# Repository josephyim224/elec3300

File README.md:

# Elec3300

This project builds an omni wheel car with a bluetooth remote controller. The omni wheel robot is based on STM32F103 with DRV8801 as motor driver. The controller is based on STM8S003.

## Car

### PCB Design

*Car PCB Top View*

*Car PCB Bottom View*

*see [schematic.pdf](car_hw/output/schematic.pdf)*

### 3D Print Components

*Car Motor Mount*

*Car Shaft A*

*Car Shaft B*

### Software

- Use STM32CubeIDE
- Refer to `/car_sw`

## Remote

### PCB Design

*Remote PCB Top View*

*Remote PCB Bottom View*

*see [schematic.pdf](remote_hw/output/schematic.pdf)*

### 3D Print Components

*Remote Case*

### Software

Setup:
1. `sudo apt-get install libusb-1.0-0-dev sdcc -y`
1. Get [stm8flash](https://github.com/vdudouyt/stm8flash)
1. Run `bash ./flash.sh` to compile and flash program

Reference: [Getting started with STM8 Development Tools on GNU/LINUX](https://www.codementor.io/@hbendali/)getting-started-with-stm8-development-tools-on-gnu-linux-zu59yo35x

Template: [stsw-stm8069](https://my.st.com/content/my_st_com/en/products/embedded-software/mcu-mpu-embedded-software/stm8-embedded-software/stsw-stm8069.html)

Library: [stm8s-sdcc](https://github.com/stecman/stm8s-sdcc)

## Final Deliverables

*Car Top*

*Car Bottom*

*Remote Top*

*Remote With Case*

## Progress
| urgency | difficulty | task | description | done? |
| --- | --- | --- | --- | --- |
| - | - | design pcb | | v |
| - | - | solder pcb | | v |
| - | - | mech design | | car(v), remote(v) |
| 0 | 0 | button | button | remote(v) | |
| 0 | 0 | led | led display | car(v), remote(v) |
| 1 | 1 | motor driver | (car) pwm & direction control | v |
| 1 | 2 | uart | communicate | car(v), remote(v) |
| 1 | 2 | i2c | communicate | car(v hardware), remote(v software) |
| 1 | 3 | mpu6050 (i2c) | port and simplify Adafruit version | car(v), remote(v) |
| 2 | 4 | ssd1306 lcd (i2c) | display line and text | car(v), remote(v) |
| 3 | 2 | ws2812b RGB led | display R/G/B | car(v), remote(x) |
| 4 | 1 | vibration motor | (remote) pwm output | x |
| 4 | 2 | 24c02 eeprom (i2c) | read and write data | x |
| 4 | ? | encoder | (car) encoder counter | v |
| 5 | 4 | gy530 TOF (i2c) | get distance | x |

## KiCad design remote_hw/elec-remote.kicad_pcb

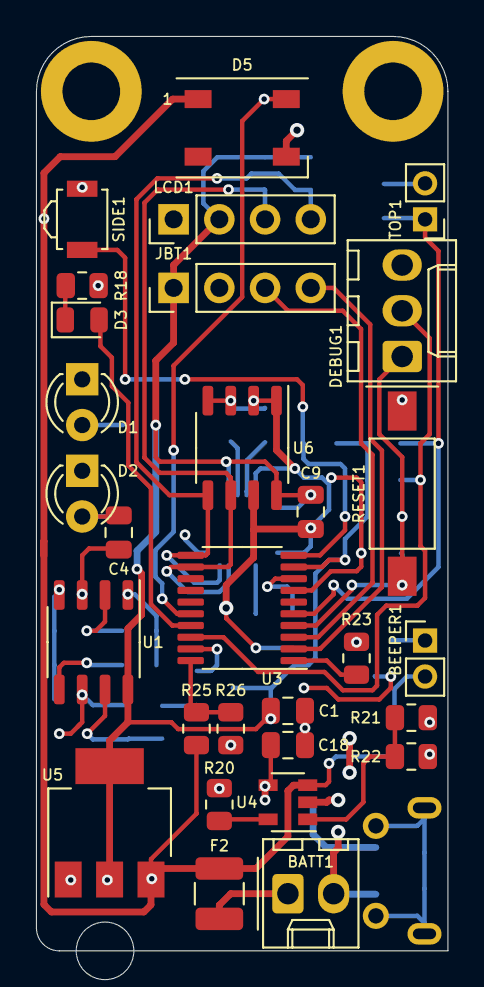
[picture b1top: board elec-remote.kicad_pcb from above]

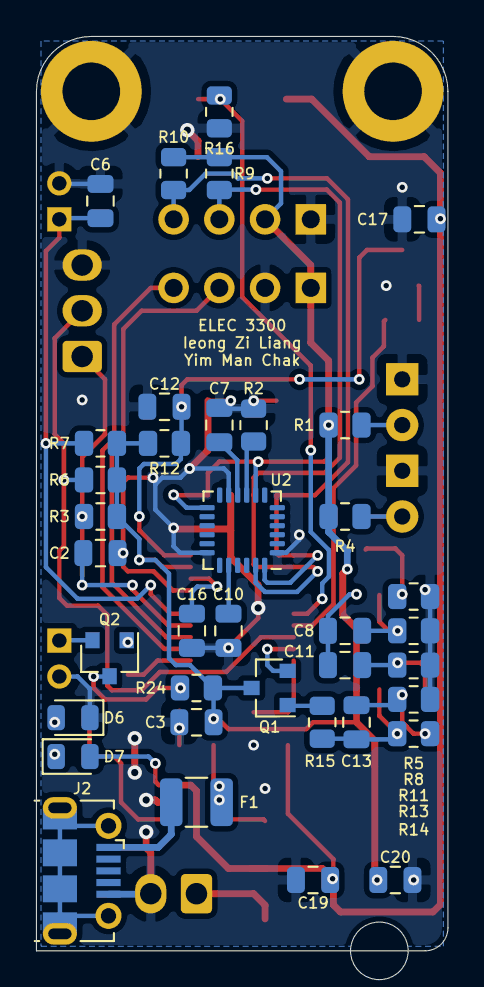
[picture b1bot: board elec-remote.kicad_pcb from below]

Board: 2 copper layers, 22.9 x 50.8 mm, 69 parts (37 on the bottom side), 40 nets.

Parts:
BATT1: BATT; Molex_KK-254_AE-6410-02A_1x02_P2.54mm_Vertical
BEEPER1: BEEPER; PinHeader_1x02_P2.00mm_Vertical
C1, C2, C4, C6, C7, C8, C9, C12, C13, C17, C20: 100n; C_0805_2012Metric
C3, C11, C16, C18, C19: 1u; C_0805_2012Metric
C10: 2200p; C_0805_2012Metric
D1: IR_Sender; LED_D3.0mm
D2: IR_Receiver; LED_D3.0mm
D3, D6, D7: LED; LED_0805_2012Metric
D5: WS2812B; LED_WS2812B_PLCC4_5.0x5.0mm_P3.2mm
DEBUG1: Conn_01x03; Molex_KK-254_AE-6410-03A_1x03_P2.54mm_Vertical
F1, F2: Fuse; Fuse_1210_3225Metric
H1, H3: MountingHole_Pad; MountingHole_3.2mm_M3_DIN965_Pad
H2: MountingHole_Pad; MountingHole_3.2mm_M3
J2: USB_B_Micro; USB_Micro-B_Molex-105017-0001
JBT1: BT; PinHeader_1x04_P2.54mm_Vertical
LCD1: LCD; PinHeader_1x04_P2.54mm_Vertical
Q1, Q2: BC817; SOT-23
R1: 220; R_0805_2012Metric
R2: 0; R_0805_2012Metric
R3, R6, R7, R9, R10, R12, R18, R21, R22, R25, R26: 4k7; R_0805_2012Metric
R4: 39k; R_0805_2012Metric
R5, R11: 68k; R_0805_2012Metric
R8: 8k2; R_0805_2012Metric
R13, R16, R23, R24: 1k; R_0805_2012Metric
R14: 470k; R_0805_2012Metric
R15: 1k8; R_0805_2012Metric
R20: 2k; R_0805_2012Metric
RESET1: SW_Push; SW_SPST_FSMSM
SIDE1: SW_Push; SW_SPST_B3U-3000P
TOP1: TOP; PinHeader_1x02_P2.00mm_Vertical
U1: LM358; SOP-8_3.9x4.9mm_P1.27mm
U2: MPU-6050; InvenSense_QFN-24_4x4mm_P0.5mm
U3: STM8S003F3P; TSSOP-20_4.4x6.5mm_P0.65mm
U4: MCP73831-2-OT; SOT-23-5
U5: AP1117-33; SOT-223-3_TabPin2
U6: 24LC00; SOP-8_3.9x4.9mm_P1.27mm

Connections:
+3V3: C1.2, C3.2, C9.2, C20.1, JBT1.1, LCD1.2, Q1.3, R1.2, R3.2, R4.2, R6.2, R7.2, R9.2, R10.2, R12.2, R24.2, U1.8, U2.8, U2.13, U3.9, U5.2, U6.8
+5V: C18.2, F1.1, U4.4
+BATT: C17.2, C19.1, D5.1, D7.2, F2.2, R25.2, U4.3, U5.3
/BATT: R25.1, R26.2, U3.20
/BEEP: R23.2, U3.1
/IR: Q1.2, U3.19
/LED0: D3.2, U3.17
/NRST: C2.2, DEBUG1.1, R3.1, RESET1.1, U3.4
/RX: JBT1.3, U3.3
/SCL: LCD1.3, R9.1, U2.23, U3.12, U6.6
/SDA: LCD1.4, R10.1, U2.24, U3.11, U6.5
/SIDE: C12.2, R12.1, SIDE1.1, U3.10
/SWIM: DEBUG1.2, R6.1, U3.18
/TOP: C6.2, R7.1, TOP1.1, U3.5
/TX: JBT1.4, U3.2
/WS2812: D5.4, R16.2, U3.16
GND: BATT1.2, BEEPER1.2, C1.1, C2.1, C3.1, C6.1, C7.1, C9.1, C10.1, C12.1, C16.1, C17.1, C18.1, C19.2, C20.2, D1.1, D2.1, D5.3, D6.1, DEBUG1.3, H1.1, H3.1, J2.5, JBT1.2, LCD1.1, R2.2, R5.1, R8.1, R11.1, R13.2, R16.1, R18.1, R20.2, R26.1, RESET1.2, SIDE1.2, TOP1.2, U1.4, U2.1, U2.11, U2.18, U3.7, U4.2, U5.1, U6.1, U6.2, U6.3, U6.4, U6.7
unnamed: BATT1.1, F2.1
unnamed: BEEPER1.1, Q2.2
unnamed: C4.1, R5.2, U1.3
unnamed: C4.2, D2.2, R4.1
unnamed: C7.2, U2.10
unnamed: C8.2, R8.2, U1.2
unnamed: C10.2, U2.20
unnamed: C11.1, R11.2, U1.5
unnamed: C8.1, C11.2, U1.1
unnamed: C13.1, R14.1, R15.2, U1.7
unnamed: C13.2, R13.1, R14.2, U1.6
unnamed: C16.2, U3.8
unnamed: D1.2, R1.1
unnamed: D3.1, R18.2
unnamed: D6.2, R21.1
unnamed: D7.1, R22.1
unnamed: F1.2, J2.1
unnamed: Q1.1, R15.1
unnamed: Q2.1, R23.1
unnamed: Q2.3, R24.1
unnamed: R2.1, U2.9
unnamed: R20.1, U4.5
unnamed: R21.2, R22.2, U4.1

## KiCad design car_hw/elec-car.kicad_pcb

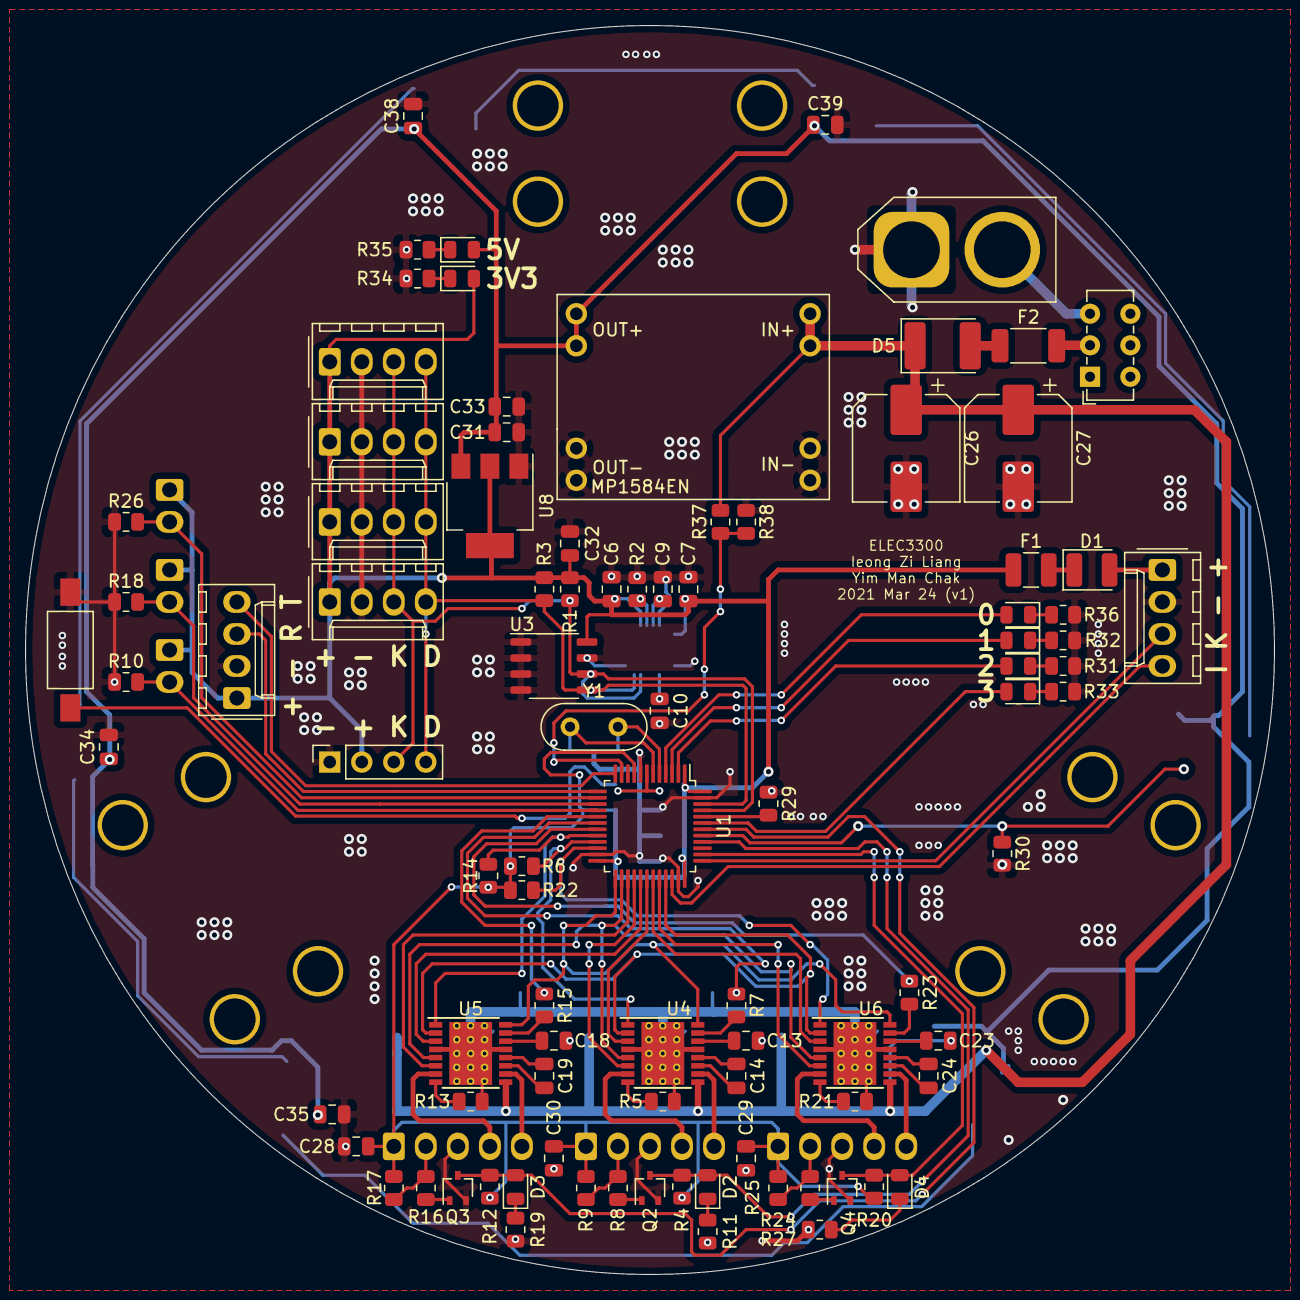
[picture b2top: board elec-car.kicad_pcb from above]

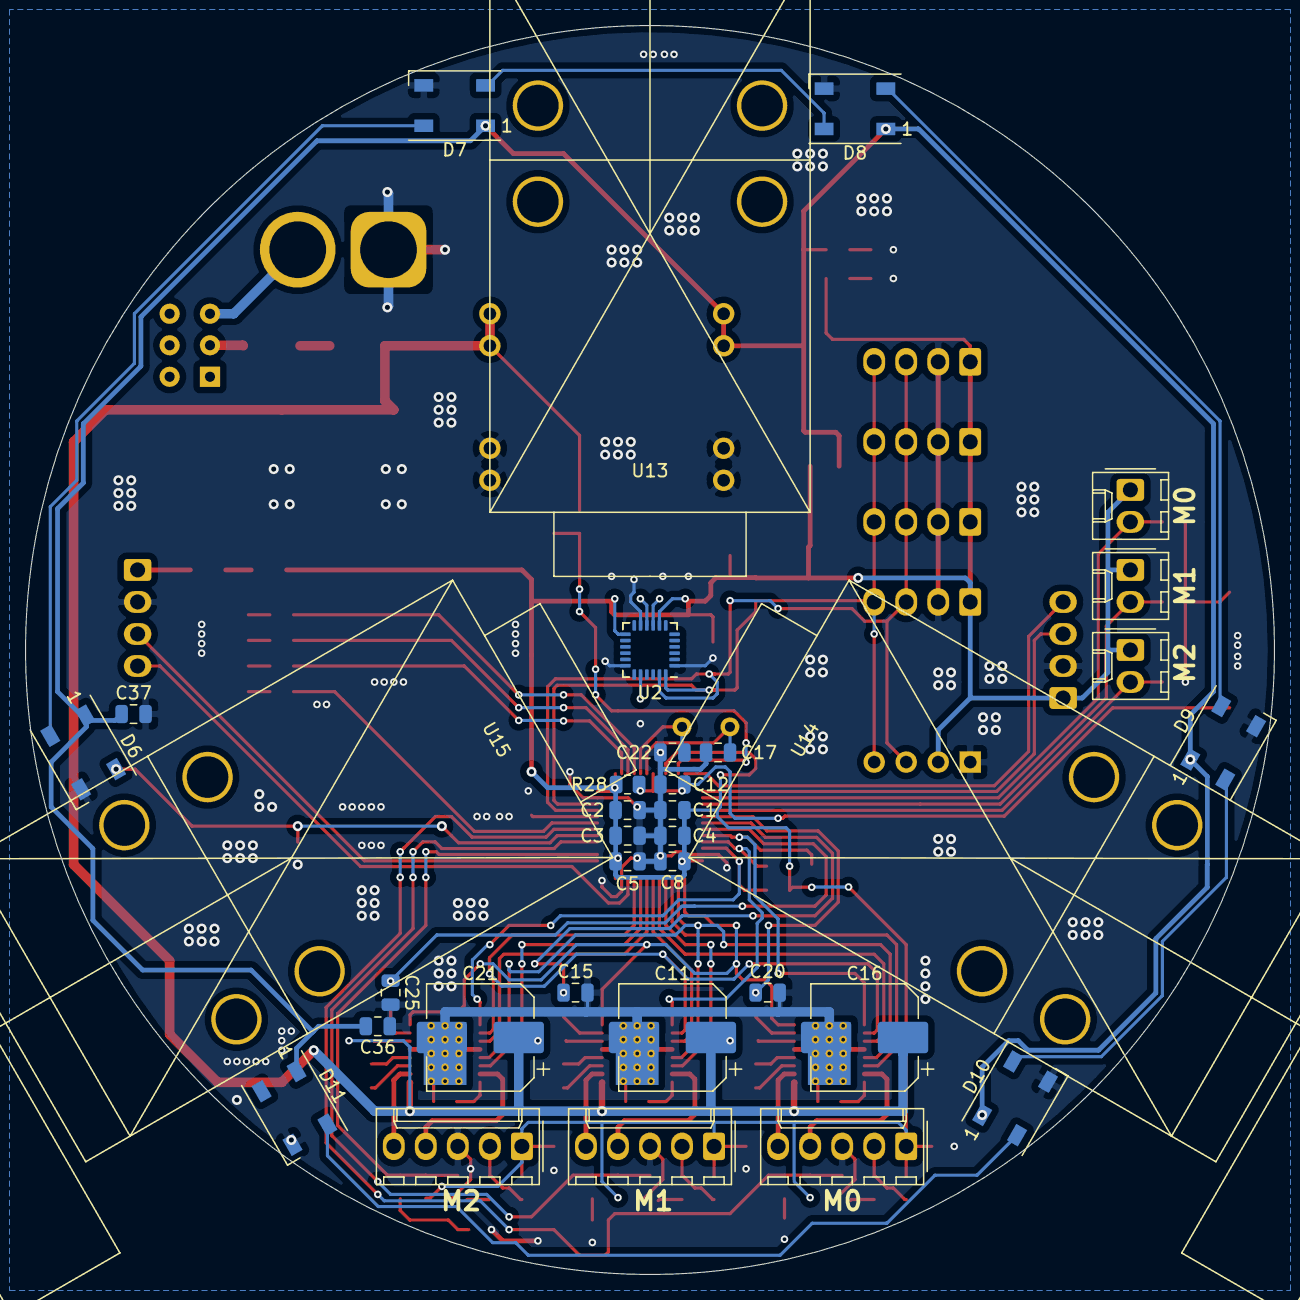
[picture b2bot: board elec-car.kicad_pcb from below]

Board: 2 copper layers, 99.1 x 99.1 mm, 127 parts (34 on the bottom side), 90 nets.

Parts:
C1, C2, C3, C4, C5, C6, C7, C9, C10, C12, C13, C14, C17, C18, C19, C22, C23, C24, C28, C29, C30, C32, C34, C35, C36, C37, C38, C39: 100n; C_0805_2012Metric
C8: 1u; C_0805_2012Metric
C11, C16, C21: 100u; CP_Elec_8x5.4
C15, C20, C25: 1n; C_0805_2012Metric
C26, C27: C; CP_Elec_8x5.4
C31, C33: 10u; C_0805_2012Metric
D1: D; D_1210_3225Metric
D2, D3, D4, D12, D13, D14, D15, D16, D17: LED; LED_0805_2012Metric
D5: D; D_2114_3652Metric
D6, D7, D8, D9, D10, D11: WS2812B; LED_WS2812B_PLCC4_5.0x5.0mm_P3.2mm
F1: Fuse; Fuse_1210_3225Metric
F2: Fuse; Fuse_2010_5025Metric
J1, J2, J9, J10, J11, J12: Conn_01x04; Molex_KK-254_AE-6410-04A_1x04_P2.54mm_Vertical
J3, J5, J7: Conn_01x05; Molex_KK-254_AE-6410-05A_1x05_P2.54mm_Vertical
J4, J6, J8: Conn_01x02; Molex_KK-254_AE-6410-02A_1x02_P2.54mm_Vertical
J13: Conn_01x02; AMASS_XT60-F_1x02_P7.20mm_Vertical
J14: Conn_01x04; PinSocket_1x04_P2.54mm_Vertical
Q2, Q3, Q4: BC818W; SOT-323_SC-70
R1, R3, R28, R30, R31, R32, R33, R34, R35, R36: 470; R_0805_2012Metric
R2, R29: 0; R_0805_2012Metric
R4, R8, R11, R12, R16, R19, R20, R24, R27: 1k; R_0805_2012Metric
R5, R13, R21: 0.2; R_0805_2012Metric
R6, R9, R14, R17, R22, R25, R38: 10k; R_0805_2012Metric
R7, R10, R15, R18, R23, R26: 100k; R_0805_2012Metric
R37: 50k; R_0805_2012Metric
SW1: SW_Push; SW_SPST_FSMSM
SW2: SW_SPDT; SW_E-Switch_EG1271_DPDT
U1: STM32F103C8Tx; LQFP-48_7x7mm_P0.5mm
U2: MPU-6050; InvenSense_QFN-24_4x4mm_P0.5mm
U3: 24LC00; SOP-8_3.9x4.9mm_P1.27mm
U4, U5, U6: DRV8801PWP; HTSSOP-16-1EP_4.4x5mm_P0.65mm_EP3.4x5mm_Mask3x3mm_ThermalVi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
U7: MP1584EN
U8: LM1117-3.3; SOT-223-3_TabPin2
U13, U14, U15: DC_Motor_wGearReduction
Y1: Crystal; Crystal_HC52-6mm_Vertical

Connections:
+5V: C31.1, C33.1, C34.1, C35.1, C36.1, C37.1, C38.1, C39.1, D6.1, D7.1, D8.1, D9.1, D10.1, D11.1, D16.2, U7.5, U7.6, U8.3
+BATT: C11.1, C13.2, C16.1, C18.2, C21.1, C23.2, C26.1, C27.1, D5.1, R37.2, U4.9, U5.9, U6.9, U7.1, U7.2
/BOOT0: R29.2, U1.44
/M0_Enable: U1.32, U6.6
/M0_Enc: D4.2, Q4.3, R20.1, U1.38
/M0_Mode0: U1.33, U4.2, U5.2, U6.2
/M0_Mode1: U1.25, U4.16, U5.16, U6.16
/M0_NTC: J8.2, R26.2, U1.14
/M0_Phase: U1.31, U6.3
/M0_Vpropi: C25.1, R23.1, U1.19
/M0_nFault: R22.2, U1.22, U6.1
/M0_nSleep: U1.26, U4.5, U5.5, U6.5
/M1_Enable: U1.27, U5.6
/M1_Enc: D3.2, Q3.3, R12.1, U1.42
/M1_NTC: J6.2, R18.2, U1.15
/M1_Phase: U1.29, U5.3
/M1_Vpropi: C20.1, R15.1, U1.17
/M1_nFault: R14.2, U1.20, U5.1
/M2_Enable: U1.28, U4.6
/M2_Enc: D2.2, Q2.3, R4.1, U1.40
/M2_NTC: J4.2, R10.2, U1.16
/M2_Phase: U1.30, U4.3
/M2_Vpropi: C15.1, R7.1, U1.18
/M2_nFault: R6.2, U1.21, U4.1
/OSC_IN: C22.1, U1.5, Y1.2
/OSC_OUT: C17.1, U1.6, Y1.1
/RX: J2.3, U1.13
/SCL: J9.3, J10.3, J11.3, J12.3, J14.3, R1.1, U1.45, U2.23, U3.6
/SDA: J9.4, J10.4, J11.4, J12.4, J14.4, R3.1, U1.46, U2.24, U3.5
/SPI_MOSI: D6.4, R30.1, U1.41
/SWCLK: J1.3, U1.37
/SWDIO: J1.4, U1.34
/TX: J2.4, U1.12
GND: C1.2, C2.2, C3.2, C4.2, C5.2, C6.2, C7.2, C8.2, C9.2, C10.2, C11.2, C12.2, C15.2, C16.2, C17.2, C20.2, C21.2, C22.2, C25.2, C26.2, C27.2, C28.1, C29.1, C30.1, C31.2, C32.2, C33.2, C34.2, C35.2, C36.2, C37.2, C38.2, C39.2, D6.3, D7.3, D8.3, D9.3, D10.3, D11.3, J1.2, J2.2, J3.3, J5.3, J7.3, J9.2, J10.2, J11.2, J12.2, J13.1, J14.1, Q2.2, Q3.2, Q4.2, R2.1, R5.1, R10.1, R11.1, R13.1, R18.1, R19.1, R21.1, R26.1, R27.1, R29.1, R30.2, R31.1, R32.1, R33.1, R34.1, R35.1, R36.1, R38.1, SW1.1, U1.8, U1.23, U1.35, U1.47, U2.1, U2.11, U2.18, U3.1, U3.2, U3.3, U3.4, U3.7, U4.4, U4.13, U4.17, U5.4, U5.13, U5.17, U6.4, U6.13, U6.17, U7.3, U7.4, U7.7, U7.8, U8.1
unnamed: C9.1, U2.10
unnamed: C10.1, U2.20
unnamed: C12.1, R28.1, SW1.2, U1.7
unnamed: C13.1, U4.14
unnamed: C14.1, U4.12
unnamed: C14.2, U4.11
unnamed: C18.1, U5.14
unnamed: C19.1, U5.12
unnamed: C19.2, U5.11
unnamed: C23.1, U6.14
unnamed: C24.1, U6.12
unnamed: C24.2, U6.11
unnamed: D1.1, F1.1
unnamed: D1.2, J1.1
unnamed: D2.1, R11.2
unnamed: D3.1, R19.2
unnamed: D4.1, R27.2
unnamed: D5.2, F2.1
unnamed: D6.2, D7.4
unnamed: D7.2, D8.4
unnamed: D8.2, D9.4
unnamed: D10.2, D11.4
unnamed: D9.2, D10.4
unnamed: D12.1, R31.2
unnamed: D12.2, U1.2
unnamed: D13.1, R32.2
unnamed: D13.2, U1.3
unnamed: D14.1, R33.2
unnamed: D14.2, U1.43
unnamed: D15.1, R34.2
unnamed: D16.1, R35.2
unnamed: D17.1, R36.2
unnamed: D17.2, U1.4
unnamed: F2.2, SW2.2
unnamed: J3.2, R8.1, R9.1
unnamed: J3.4, U4.7
unnamed: J3.5, U4.10
unnamed: J5.2, R16.1, R17.1
unnamed: J5.4, U5.7
unnamed: J5.5, U5.10
unnamed: J7.2, R24.1, R25.1
unnamed: J7.4, U6.7
unnamed: J7.5, U6.10
unnamed: J13.2, SW2.3
unnamed: Q2.1, R8.2
unnamed: Q3.1, R16.2
unnamed: Q4.1, R24.2
unnamed: R2.2, U2.9
unnamed: R5.2, U4.8
unnamed: R7.2, U4.15
unnamed: R13.2, U5.8
unnamed: R15.2, U5.15
unnamed: R21.2, U6.8
unnamed: R23.2, U6.15
unnamed: R37.1, R38.2, U1.11
VCC: C1.1, C2.1, C3.1, C4.1, C5.1, C6.1, C7.1, C8.1, C28.2, C29.2, C30.2, C32.1, D15.2, F1.2, J2.1, J3.1, J4.1, J5.1, J6.1, J7.1, J8.1, J9.1, J10.1, J11.1, J12.1, J14.2, R1.2, R3.2, R4.2, R6.1, R9.2, R12.2, R14.1, R17.2, R20.2, R22.1, R25.2, R28.2, U1.1, U1.9, U1.24, U1.36, U1.48, U2.8, U2.13, U3.8, U8.2

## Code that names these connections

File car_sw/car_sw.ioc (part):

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PA11.GPIO_Speed=GPIO_SPEED_FREQ_HIGH
PB13.GPIOParameters=GPIO_Speed,PinState,GPIO_PuPd,GPIO_Label
Mcu.UserName=STM32F103C8Tx
PB10.GPIO_PuPd=GPIO_PULLUP
PA10.GPIO_PuPd=GPIO_PULLDOWN
PC13-TAMPER-RTC.GPIOParameters=GPIO_Speed,GPIO_PuPd,GPIO_Label
PB14.GPIO_Label=M1_ENABLE
PA12.GPIOParameters=GPIO_Speed,GPIO_PuPd,GPIO_Label
PA9.GPIOParameters=GPIO_Speed,GPIO_PuPd,GPIO_Label
PA11.GPIOParameters=GPIO_Speed,GPIO_Label
PA6.GPIO_Label=M2_NTC
PB0.GPIO_Label=M2_VPROPI
PB6.GPIO_Label=M0_ENC
PB11.GPIO_PuPd=GPIO_PULLUP
PB13.GPIO_Label=M_nSLEEP
PB11.Signal=GPIO_Input
PB13.Signal=GPIO_Output
PB15.Signal=TIM1_CH3N
PC15-OSC32_OUT.GPIO_Label=LED0
RCC.SYSCLKSource=RCC_SYSCLKSOURCE_PLLCLK
PB5.GPIOParameters=GPIO_Speed,GPIO_PuPd,GPIO_Label
PD1-OSC_OUT.Signal=RCC_OSC_OUT
PA15.GPIO_Label=M1_ENC
PB4.GPIOParameters=GPIO_Label
PA12.Signal=GPIO_Output
PB6.Signal=S_TIM4_CH1
PA8.GPIOParameters=GPIO_Speed,GPIO_PuPd,GPIO_Label
PB2.Signal=GPIO_Input
PB12.GPIO_Label=M_MODE1
PB0.GPIOParameters=GPIO_Label
PA1.GPIOParameters=GPIO_Label
PA14.Mode=Serial_Wire
PB14.Mode=PWM Generation2 CH2N
PB1.GPIO_Label=M0_VPROPI
PA10.GPIO_Label=M0_PHASE
PB7.Signal=GPIO_Output
PA8.Signal=GPIO_Output
PC13-TAMPER-RTC.GPIO_Speed=GPIO_SPEED_FREQ_HIGH
PB6.GPIOParameters=GPIO_PuPd,GPIO_Label
PB2.GPIO_PuPd=GPIO_PULLUP
PC14-OSC32_IN.GPIOParameters=GPIO_Speed,GPIO_PuPd,GPIO_Label
PC14-OSC32_IN.GPIO_Speed=GPIO_SPEED_FREQ_HIGH
PB7.GPIO_Label=LED3
Mcu.Package=LQFP48
PB9.Signal=I2C1_SDA
PB1.Signal=ADCx_IN9
PA6.Signal=ADCx_IN6
PC13-TAMPER-RTC.GPIO_PuPd=GPIO_PULLDOWN
PA10.Signal=GPIO_Output
PA15.Signal=S_TIM2_CH1_ETR
PA5.GPIOParameters=GPIO_Label
PB14.GPIOParameters=GPIO_Speed,GPIO_Label
PA10.GPIO_Speed=GPIO_SPEED_FREQ_HIGH
PB5.GPIO_Speed=GPIO_SPEED_FREQ_HIGH
PB5.GPIO_Label=WS2812B
PC14-OSC32_IN.GPIO_Label=LED1
PC15-OSC32_OUT.GPIO_Speed=GPIO_SPEED_FREQ_HIGH
PB10.GPIOParameters=GPIO_PuPd,GPIO_Label
PC15-OSC32_OUT.GPIOParameters=GPIO_Speed,GPIO_PuPd,GPIO_Label
PA12.GPIO_PuPd=GPIO_PULLDOWN
PA4.GPIO_Label=M0_NTC
PA8.GPIO_Speed=GPIO_SPEED_FREQ_HIGH
PA12.GPIO_Speed=GPIO_SPEED_FREQ_HIGH
PB4.Signal=S_TIM3_CH1
PA3.Signal=USART2_RX
PB7.GPIO_Speed=GPIO_SPEED_FREQ_HIGH
PA6.GPIOParameters=GPIO_Label
PB7.GPIO_PuPd=GPIO_PULLDOWN
PD1-OSC_OUT.Mode=HSE-External-Oscillator
PA15.GPIOParameters=GPIO_Label
PA9.GPIO_Label=M2_PHASE
PB6.GPIO_PuPd=GPIO_PULLDOWN
PB11.GPIO_Label=M0_nFAULT
PC13-TAMPER-RTC.Signal=GPIO_Output
PA11.GPIO_Label=M0_ENABLE
PD0-OSC_IN.Signal=RCC_OSC_IN
PC14-OSC32_IN.Signal=GPIO_Output
PA9.GPIO_PuPd=GPIO_PULLDOWN
PA12.GPIO_Label=M_MODE0
PA3.Mode=Asynchronous
PA13.Signal=SYS_JTMS-SWDIO
PA8.GPIO_Label=M1_PHASE
PB14.GPIO_Speed=GPIO_SPEED_FREQ_HIGH
PB10.GPIO_Label=M2_nFAULT
PB7.GPIOParameters=GPIO_Speed,GPIO_PuPd,GPIO_Label
PB9.Mode=I2C
PB2.GPIOParameters=GPIO_PuPd,GPIO_Label
PA9.Signal=GPIO_Output
PB13.GPIO_Speed=GPIO_SPEED_FREQ_HIGH
PB11.GPIOParameters=GPIO_PuPd,GPIO_Label
PC15-OSC32_OUT.Signal=GPIO_Output
PA1.Signal=ADCx_IN1
PB12.GPIO_Speed=GPIO_SPEED_FREQ_HIGH
PD0-OSC_IN.Mode=HSE-External-Oscillator
PB10.Signal=GPIO_Input
PB14.Signal=TIM1_CH2N
PA5.Signal=ADCx_IN5
board=custom
PC13-TAMPER-RTC.GPIO_Label=LED2
PB15.Mode=PWM Generation3 CH3N
PB13.GPIO_PuPd=GPIO_PULLUP
PB13.PinState=GPIO_PIN_RESET
PB4.GPIO_Label=M2_ENC
PB15.GPIO_Label=M2_ENABLE
PB15.GPIO_Speed=GPIO_SPEED_FREQ_HIGH
PA1.GPIO_Label=BATT
PA10.GPIOParameters=GPIO_Speed,GPIO_PuPd,GPIO_Label
PC15-OSC32_OUT.GPIO_PuPd=GPIO_PULLDOWN
PA4.GPIOParameters=GPIO_Label
PB15.GPIOParameters=GPIO_Speed,GPIO_Label
PA13.Mode=Serial_Wire
Mcu.Name=STM32F103C(8-B)Tx
PA2.Signal=USART2_TX
PA4.Signal=ADCx_IN4
RCC.SYSCLKFreq_VALUE=72000000
PB5.Signal=GPIO_Output
PA7.GPIO_Label=M1_VPROPI
PA5.GPIO_Label=M1_NTC
PB5.GPIO_PuPd=GPIO_PULLDOWN
PA11.Signal=S_TIM1_CH4
PA14.Signal=SYS_JTCK-SWCLK
PB2.GPIO_Label=M1_nFAULT
PA8.GPIO_PuPd=GPIO_PULLDOWN
PB8.Mode=I2C
PA2.Mode=Asynchronous
PA9.GPIO_Speed=GPIO_SPEED_FREQ_HIGH
PB8.Signal=I2C1_SCL
PC14-OSC32_IN.GPIO_PuPd=GPIO_PULLDOWN
PB12.GPIO_PuPd=GPIO_PULLDOWN
PB0.Signal=ADCx_IN8
PA7.GPIOParameters=GPIO_Label
PB12.GPIOParameters=GPIO_Speed,GPIO_PuPd,GPIO_Label
PB12.Signal=GPIO_Output
PB1.GPIOParameters=GPIO_Label
PA7.Signal=ADCx_IN7

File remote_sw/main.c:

/**
  ******************************************************************************
  * @file    GPIO_Toggle\main.c
  * @author  MCD Application Team
  * @version V2.0.4
  * @date    26-April-2018
  * @brief   This file contains the main function for GPIO Toggle example.
  ******************************************************************************
  * @attention
  *
  * <h2><center>&copy; COPYRIGHT 2014 STMicroelectronics</center></h2>
  *
  * Licensed under MCD-ST Liberty SW License Agreement V2, (the "License");
  * You may not use this file except in compliance with the License.
  * You may obtain a copy of the License at:
  *
  *        http://www.st.com/software_license_agreement_liberty_v2
  *
  * Unless required by applicable law or agreed to in writing, software 
  * distributed under the License is distributed on an "AS IS" BASIS, 
  * WITHOUT WARRANTIES OR CONDITIONS OF ANY KIND, either express or implied.
  * See the License for the specific language governing permissions and
  * limitations under the License.
  *
  ******************************************************************************
  */

/* Includes ------------------------------------------------------------------*/
#include "main.h"
#include "SSD1306.h"
#include "MPU6050.h"

/**
  * @addtogroup GPIO_Toggle
  * @{
  */

/* Private typedef -----------------------------------------------------------*/
/* Private define ------------------------------------------------------------*/
/* Evalboard I/Os configuration */
/* Private macro -------------------------------------------------------------*/
/* Private variables ---------------------------------------------------------*/
extern struct MPU6050 mpu6050;
/* Private function prototypes -----------------------------------------------*/
void Delay(uint16_t nCount);
void BT_Send(uint8_t *, uint8_t);
/* Private functions ---------------------------------------------------------*/

void initPeripherals();

/* Public functions ----------------------------------------------------------*/

/**
  * @brief  Main program.
  * @param  None
  * @retval None
  */
void main(void)
{
  initPeripherals();

  uint8_t tick = 0;
  uint8_t mode = 0;
  uint8_t topStart = 0;
  uint8_t topped = 0;
  while (1)
  {
    uint8_t top = !GPIO_ReadInputPin(TOP_BUTTON_GPIO_PORT, TOP_BUTTON_GPIO_PIN);
    uint8_t side = !GPIO_ReadInputPin(SIDE_BUTTON_GPIO_PORT, SIDE_BUTTON_GPIO_PIN);

    if (tick % 10 == 0)
    {
      GPIO_WriteReverse(LED0_GPIO_PORT, LED0_GPIO_PIN);

      if (top)
      {
        if (!topped)
          topStart = tick;
        topped = 1;
      }
      else if (topped)
      {
        topped = 0;
        if (tick - topStart < 20)
          mode = mode ? 0 : 1;
      }

      if (top == mode || side)
      {
        uint16_t volt = (uint16_t)((uint32_t)100 * ADC1_GetConversionValue() * 4 / 696);

        clearDisplay();
        drawString(0, 0, "ti", 2);
        drawUint16(24, 0, tick);
        drawString(0, 8, "vo", 2);
        drawUint16(24, 8, volt);
        drawUint16(0, 16, mpu6050.buffer[0]);
        drawUint16(64, 16, mpu6050.buffer[1]);

        drawUint16(72, 0, mpu6050.who_am_i);

        if (volt < 360)
          drawString(0, 24, "LOW BATT", 8);
        if (top)
          drawString(54, 24, "TOP", 3);
        if (side)
          drawString(78, 24, "SIDE", 4);

        display();
      }
    }

    mpu6050_readData();
    for (uint8_t i = 0; i < 2; ++i)
    {
      BT_Send("123", 3);
      BT_Send(mpu6050.buffer, 14);
      BT_Send(&top, 1);
      BT_Send(&side, 1);
      BT_Send("456", 3);
    }

    tick += 1;
  }
}

void initPeripherals()
{
  // wait for clock to settle
  for (uint16_t i = 0; i < 0xffff; ++i)
    ;

  disableInterrupts();

  // clk init
  CLK->ICKR = CLK_ICKR_RESET_VALUE;
  CLK->ECKR = CLK_ECKR_RESET_VALUE;
  CLK->SWR = CLK_SWR_RESET_VALUE;
  CLK->SWCR = CLK_SWCR_RESET_VALUE;
  CLK->CKDIVR = CLK_CKDIVR_RESET_VALUE;
  CLK->PCKENR1 = CLK_PCKENR1_RESET_VALUE;
  CLK->PCKENR2 = CLK_PCKENR2_RESET_VALUE;
  CLK->CSSR = CLK_CSSR_RESET_VALUE;
  CLK->CCOR = CLK_CCOR_RESET_VALUE;
  while ((CLK->CCOR & CLK_CCOR_CCOEN) != 0)
    ;
  CLK->CCOR = CLK_CCOR_RESET_VALUE;
  CLK->HSITRIMR = CLK_HSITRIMR_RESET_VALUE;
  CLK->SWIMCCR = CLK_SWIMCCR_RESET_VALUE;
  CLK->CKDIVR &= (uint8_t)(~CLK_CKDIVR_HSIDIV);
  CLK->CKDIVR |= (uint8_t)0;

  // gpio init
  GPIO_Init(TOP_BUTTON_GPIO_PORT, TOP_BUTTON_GPIO_PIN, GPIO_MODE_IN_FL_NO_IT);
  GPIO_Init(SIDE_BUTTON_GPIO_PORT, SIDE_BUTTON_GPIO_PIN, GPIO_MODE_IN_FL_NO_IT);
  GPIO_Init(LED0_GPIO_PORT, LED0_GPIO_PIN, GPIO_MODE_OUT_PP_LOW_FAST);

  // i2c init
  GPIO_Init(SCL_GPIO_PORT, SCL_GPIO_PIN, GPIO_MODE_OUT_OD_HIZ_FAST);
  GPIO_Init(SDA_GPIO_PORT, SDA_GPIO_PIN, GPIO_MODE_OUT_OD_HIZ_FAST);

  // uart
  UART1_DeInit();
  UART1_Init(38400, UART1_WORDLENGTH_8D, UART1_STOPBITS_1, UART1_PARITY_NO,
             (UART1_SyncMode_TypeDef)(UART1_SYNCMODE_CLOCK_ENABLE | UART1_SYNCMODE_CPOL_LOW | UART1_SYNCMODE_CPHA_MIDDLE | UART1_SYNCMODE_LASTBIT_ENABLE),
             UART1_MODE_TXRX_ENABLE);
  UART1_Cmd(ENABLE);

  // ssd1306
  ssd1306_begin();
  clearDisplay();

  // mpu6050
  mpu6050_begin();

  // adc1
  ADC1_DeInit();
  ADC1_Init(ADC1_CONVERSIONMODE_CONTINUOUS, ADC1_CHANNEL_4, ADC1_PRESSEL_FCPU_D8,
            ADC1_EXTTRIG_TIM, DISABLE, ADC1_ALIGN_RIGHT, ADC1_SCHMITTTRIG_CHANNEL4,
            DISABLE);
  ADC1_StartConversion();

  enableInterrupts();
}

/**
  * @brief Delay
  * @param nCount
  * @retval None
  */
void Delay(uint16_t nCount)
{
  /* Decrement nCount value */
  while (nCount != 0)
  {
    nCount--;
  }
}

void BT_Send(uint8_t *data, uint8_t n)
{
  for (uint8_t i = 0; i < n; ++i)
  {
    while (!((UART1->SR & (uint8_t)UART1_FLAG_TXE) != (uint8_t)0x00))
    {
    }
    UART1_SendData8(data[i]);
  }
}

#ifdef USE_FULL_ASSERT

/**
  * @brief  Reports the name of the source file and the source line number
  *   where the assert_param error has occurred.
  * @param file: pointer to the source file name
  * @param line: assert_param error line source number
  * @retval None
  */
void assert_failed(uint8_t *file, uint32_t line)
{
  /* User can add his own implementation to report the file name and line number,
     ex: printf("Wrong parameters value: file %s on line %d\r\n", file, line) */

  /* Infinite loop */
  while (1)
  {
  }
}
#endif

/**
  * @}
  */

/************************ (C) COPYRIGHT STMicroelectronics *****END OF FILE****/

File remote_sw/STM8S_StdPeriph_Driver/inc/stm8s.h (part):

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
#define CLK_HSITRIMR_HSITRIM ((uint8_t)0x07) /*!< High speed internal oscillator trimmer */

#define CLK_SWIMCCR_SWIMDIV  ((uint8_t)0x01) /*!< SWIM Clock Dividing Factor */

/**
  * @}
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#define EXTI_CR1_PBIS ((uint8_t)0x0C) /*!< PORTB external interrupt sensitivity bits mask */
#define EXTI_CR1_PAIS ((uint8_t)0x03) /*!< PORTA external interrupt sensitivity bits mask */

#define EXTI_CR2_TLIS ((uint8_t)0x04) /*!< Top level interrupt sensitivity bit mask */
#define EXTI_CR2_PEIS ((uint8_t)0x03) /*!< PORTE external interrupt sensitivity bits mask */

/**
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  */

#define RST_SR_EMCF   ((uint8_t)0x10) /*!< EMC reset flag bit mask */
#define RST_SR_SWIMF  ((uint8_t)0x08) /*!< SWIM reset flag bit mask */
#define RST_SR_ILLOPF ((uint8_t)0x04) /*!< Illegal opcode reset flag bit mask */
#define RST_SR_IWDGF  ((uint8_t)0x02) /*!< IWDG reset flag bit mask */
#define RST_SR_WWDGF  ((uint8_t)0x01) /*!< WWDG reset flag bit mask */
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  * @{
  */

#define CFG_GCR_SWD ((uint8_t)0x01) /*!< Swim disable bit mask */
#define CFG_GCR_AL  ((uint8_t)0x02) /*!< Activation Level bit mask */

/**
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
#define AWU ((AWU_TypeDef *) AWU_BaseAddress)

#define BEEP ((BEEP_TypeDef *) BEEP_BaseAddress)

#if defined (STM8S208) || defined (STM8AF52Ax)
 #define CAN ((CAN_TypeDef *) CAN_BaseAddress)
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
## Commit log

2021-04-01 feat: init hardware
2021-04-01 feat: added datasheet
2021-04-01 feat: init car project
2021-04-01 feat: init remote project
2021-04-01 feat: add progress table
2021-04-01 fix: progress spelling
2021-04-03 fix: ignore files
2021-04-03 feat: car SSD1306 ready
2021-04-03 feat: soft WS2812B
2021-04-03 feat: update progress
2021-04-03 feat: remote fix compile script
2021-04-03 feat: update flash script
2021-04-08 feat: testing remote LCD
2021-04-08 feat: added MCP73831 datasheet
2021-04-11 feat: cat motor & encoder work
2021-04-12 feat: car mech
2021-04-13 feat: car mech update motor mount
2021-04-13 feat: car sw mpu6050 drv8081 draft code
2021-04-14 feat: car sw motor ready
2021-04-14 fix: car sw clean up
2021-04-14 feat: car sw mpu6050 working
2021-04-30 feat: 8051 soft i2c
2021-04-30 feat: remote sw soft i2c, lcd ready
2021-04-30 feat: too happy forgot to include files changed
2021-04-30 feat: remote sw stripped mpu6050
2021-05-01 feat: remote sw mpu6050 & bt ready
2021-05-01 feat: add draw int function and update communication protocol
2021-05-01 feat: low batt warning
2021-05-01 feat: top button
2021-05-01 feat: display when top is pressed
2021-05-01 feat: bt send twice, display optimize
2021-05-01 feat: mpu6050 added check who_am_i
2021-05-01 feat: buggy toggle mode
2021-05-01 added blue, pid, working on MPU6050
2021-05-01 feat: car sw change start seq
2021-05-01 feat: change remote msg seq
2021-05-01 minor fix
2021-05-02 feat: remove test code and add remote mech files
2021-05-03 feat: fix remote delay time
2021-05-03 feat: proposal, report, update readme
2021-05-03 sw final update
2021-05-03 feat: added final report
2021-05-03 feat: restructure folder
2021-12-29 chore: update readme and clean up
2021-12-29 chore: change 3D print previews to png
